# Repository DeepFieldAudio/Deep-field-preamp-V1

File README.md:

# Deep Field Preamp V1

A 4-way DIY dub preamp — open source, free, and built to be modified.

<!-- Render generated with:
     kicad-cli pcb render -o docs/images/board-top.png --quality high \
       --width 1800 --height 1080 --side top --background opaque --zoom 1.35 \
       hardware/deep-field-preamp.kicad_pcb
     Replace with a photo of a built unit when you have one. -->

## Features

- 4-way crossover with kill switches and level control per band
- 4-band parametric EQ
- 12-band graphic EQ
- Phono and line inputs for music sources
- 2 aux inputs
- 1 mic input
- 2 FX loops

## Project status

| Item | Version |
| --- | --- |
| Schematic / PCB source | V1 |
| Schematic PDF | V1 rev2 |
| Gerbers | V1.2 |

> **Note:** the source files, the PDF and the gerbers currently carry three
> different version labels. If you are ordering boards, treat
> `production/v1.2/` as the authoritative set and check it against the source
> before committing to a run.

## Repository layout

```
hardware/          KiCad 9 project — schematic, PCB and project file
docs/              Schematic PDF and build documentation
production/v1.2/   Gerbers and drill files, ready to send to a fab house
```

## Building one

1. **Order the boards.** Upload `production/v1.2/deep-field-preamp-v1.2-gerbers.zip`
   to your fab house of choice — it contains the gerbers, both drill files and
   the job file.
2. **Get the parts.** <!-- TODO: export a BOM from KiCad (File → Export → BOM)
   and commit it as docs/bom.csv, then link it here. -->
3. **Open the design.** `hardware/deep-field-preamp.kicad_pro` opens in
   KiCad 9.0 or newer. The schematic is also in `docs/` as a PDF if you just
   want to read it.

## Contributing

If you find a mistake I made, or a way to improve the design, please open an
issue or a pull request — I would rather have it fixed in the open than in
someone's private fork. And if you build your own Deep Field, share it! I would
love to see your builds.

## Licence

This work shall remain open source and free.

- **Hardware** (schematics, PCB layout, gerbers): [CERN Open Hardware Licence
  Version 2 — Strongly Reciprocal](LICENSE-hardware.txt) (CERN-OHL-S-2.0)
- **Documentation** (PDF, images, this README): [Creative Commons
  Attribution-ShareAlike 4.0 International](LICENSE-docs.txt) (CC BY-SA 4.0)

Both are share-alike: if you make your own version of this preamp, you are free
to build it, sell it and modify it, but you must publish your changes under the
same conditions I did.

## Contact

Deep Field Audio on Instagram and Facebook.

---

All you have here is work I spent countless hours on, and that I'm really happy
to share with you.

— Nélo Breuiller

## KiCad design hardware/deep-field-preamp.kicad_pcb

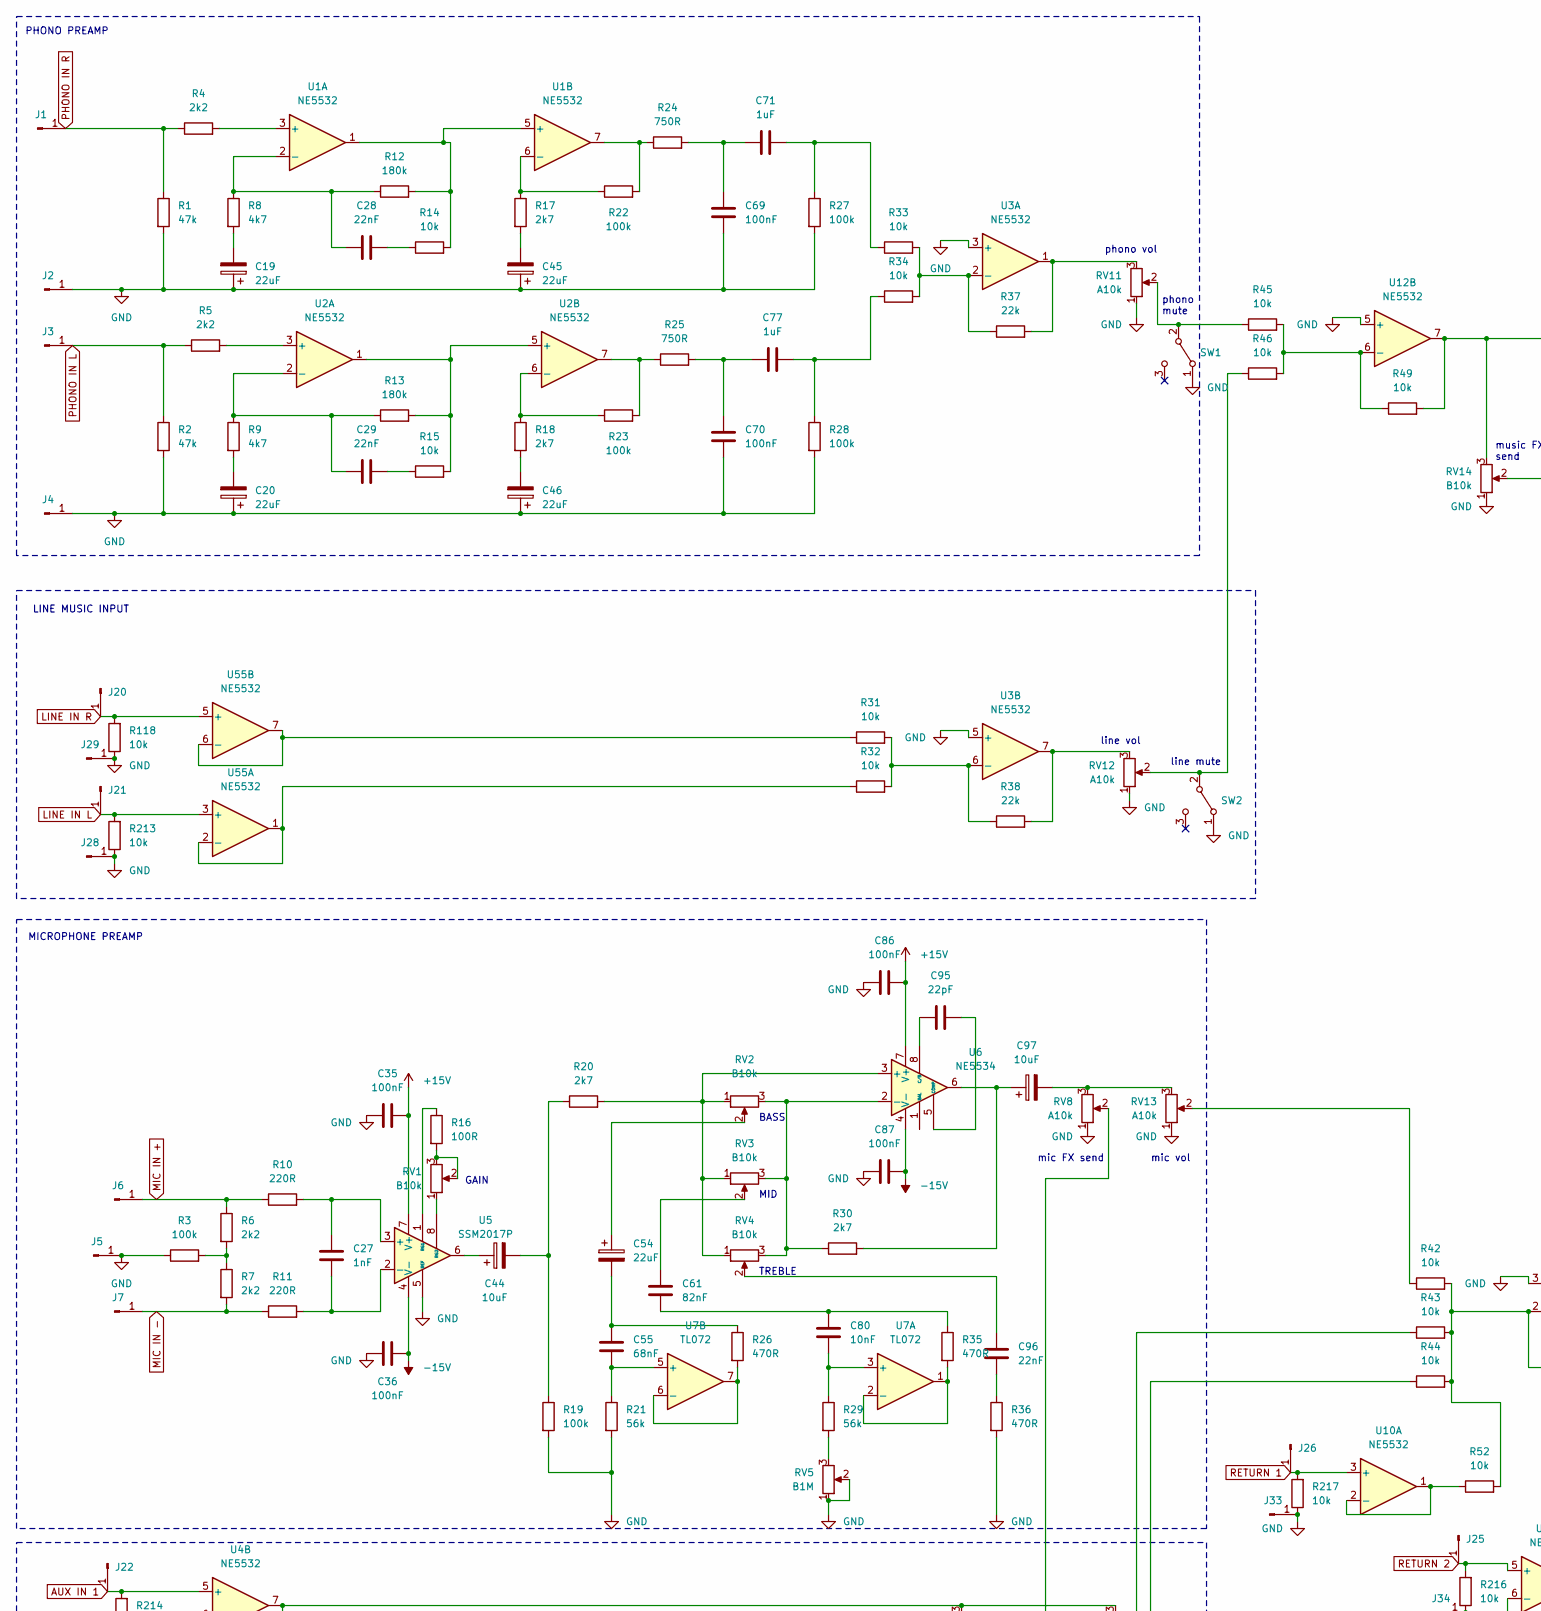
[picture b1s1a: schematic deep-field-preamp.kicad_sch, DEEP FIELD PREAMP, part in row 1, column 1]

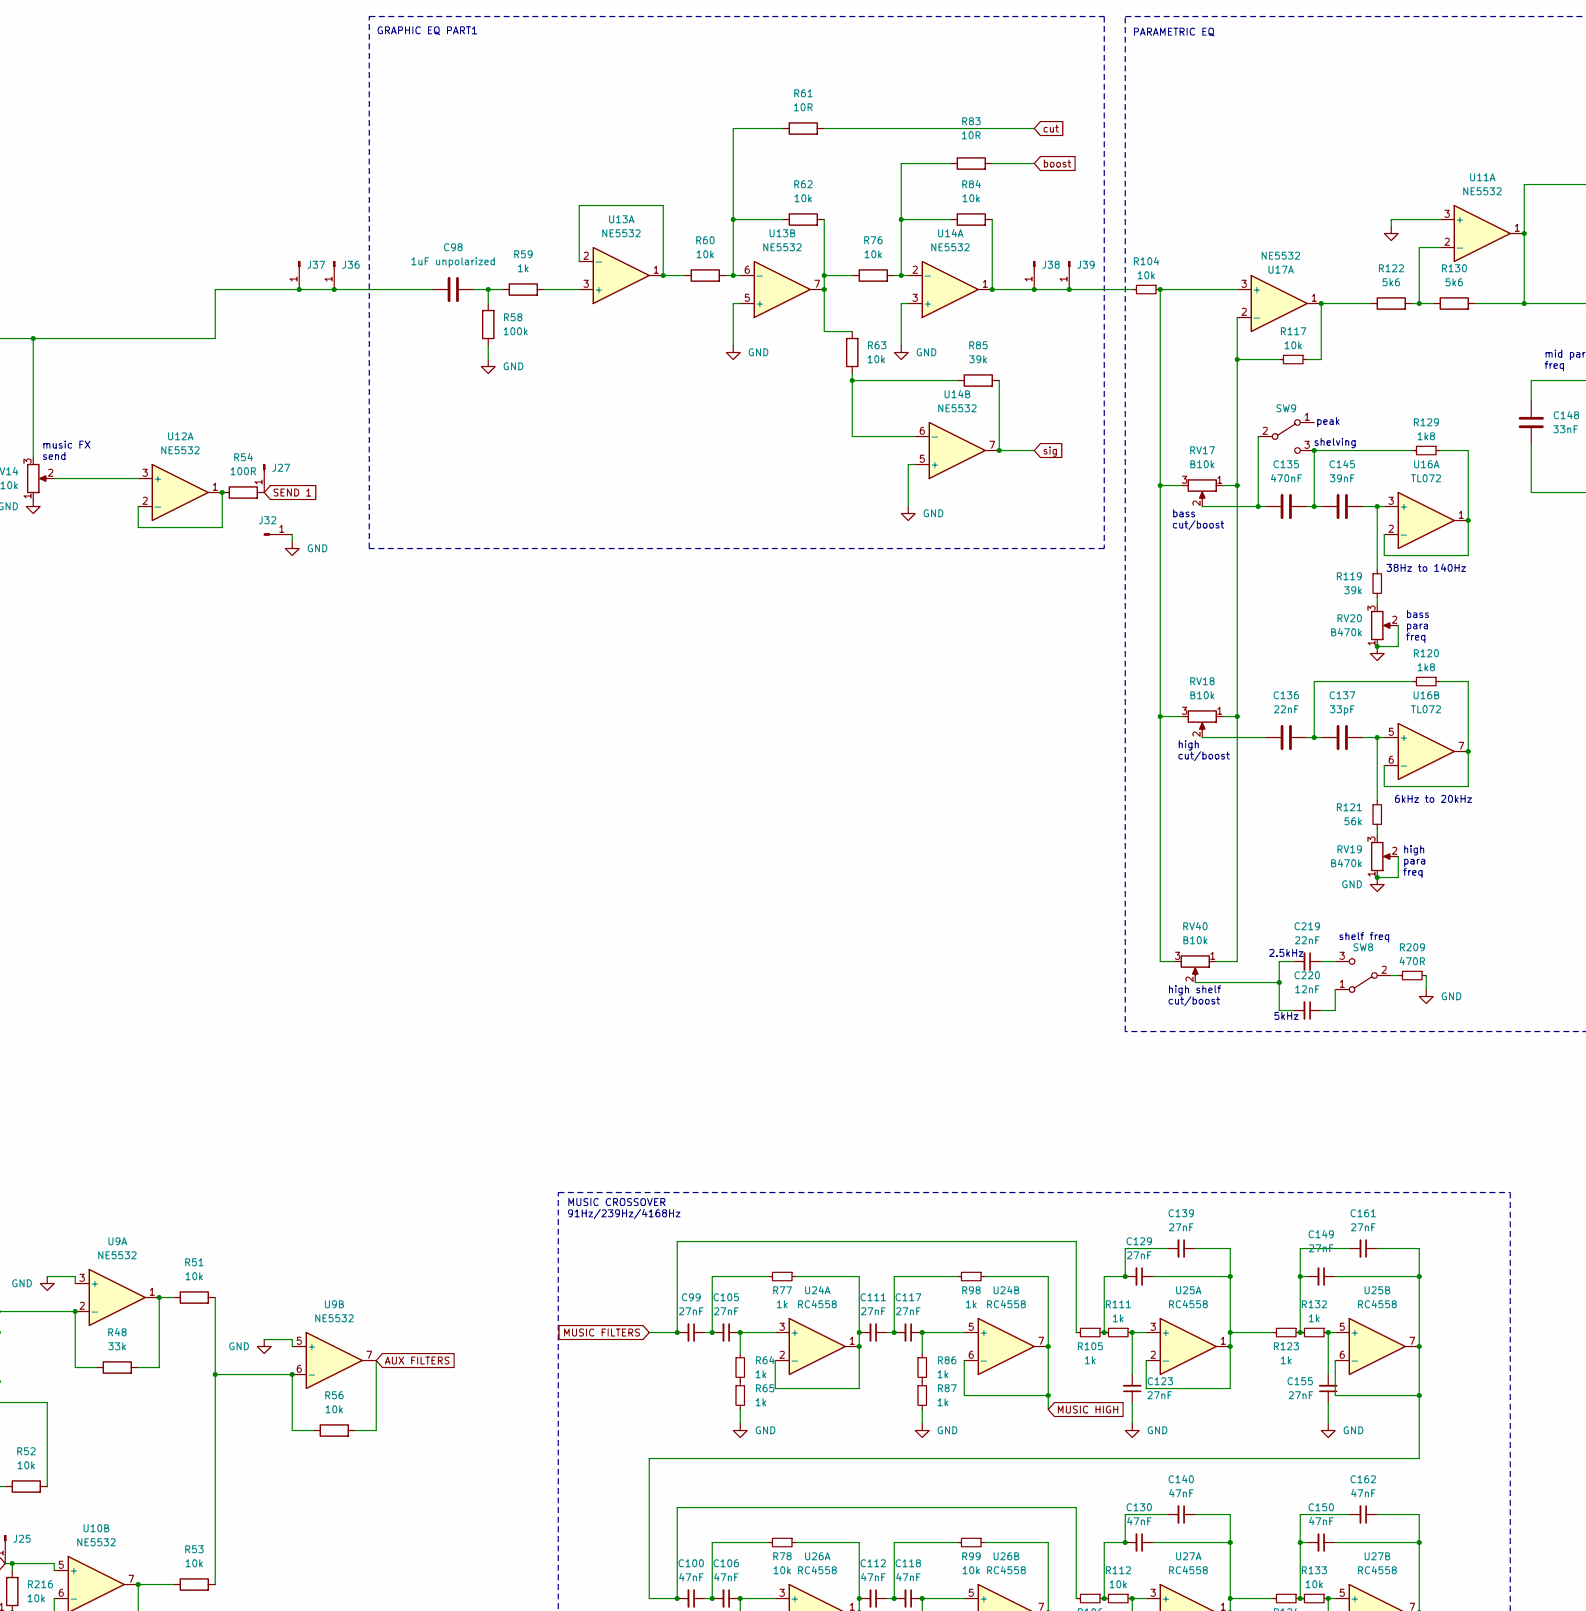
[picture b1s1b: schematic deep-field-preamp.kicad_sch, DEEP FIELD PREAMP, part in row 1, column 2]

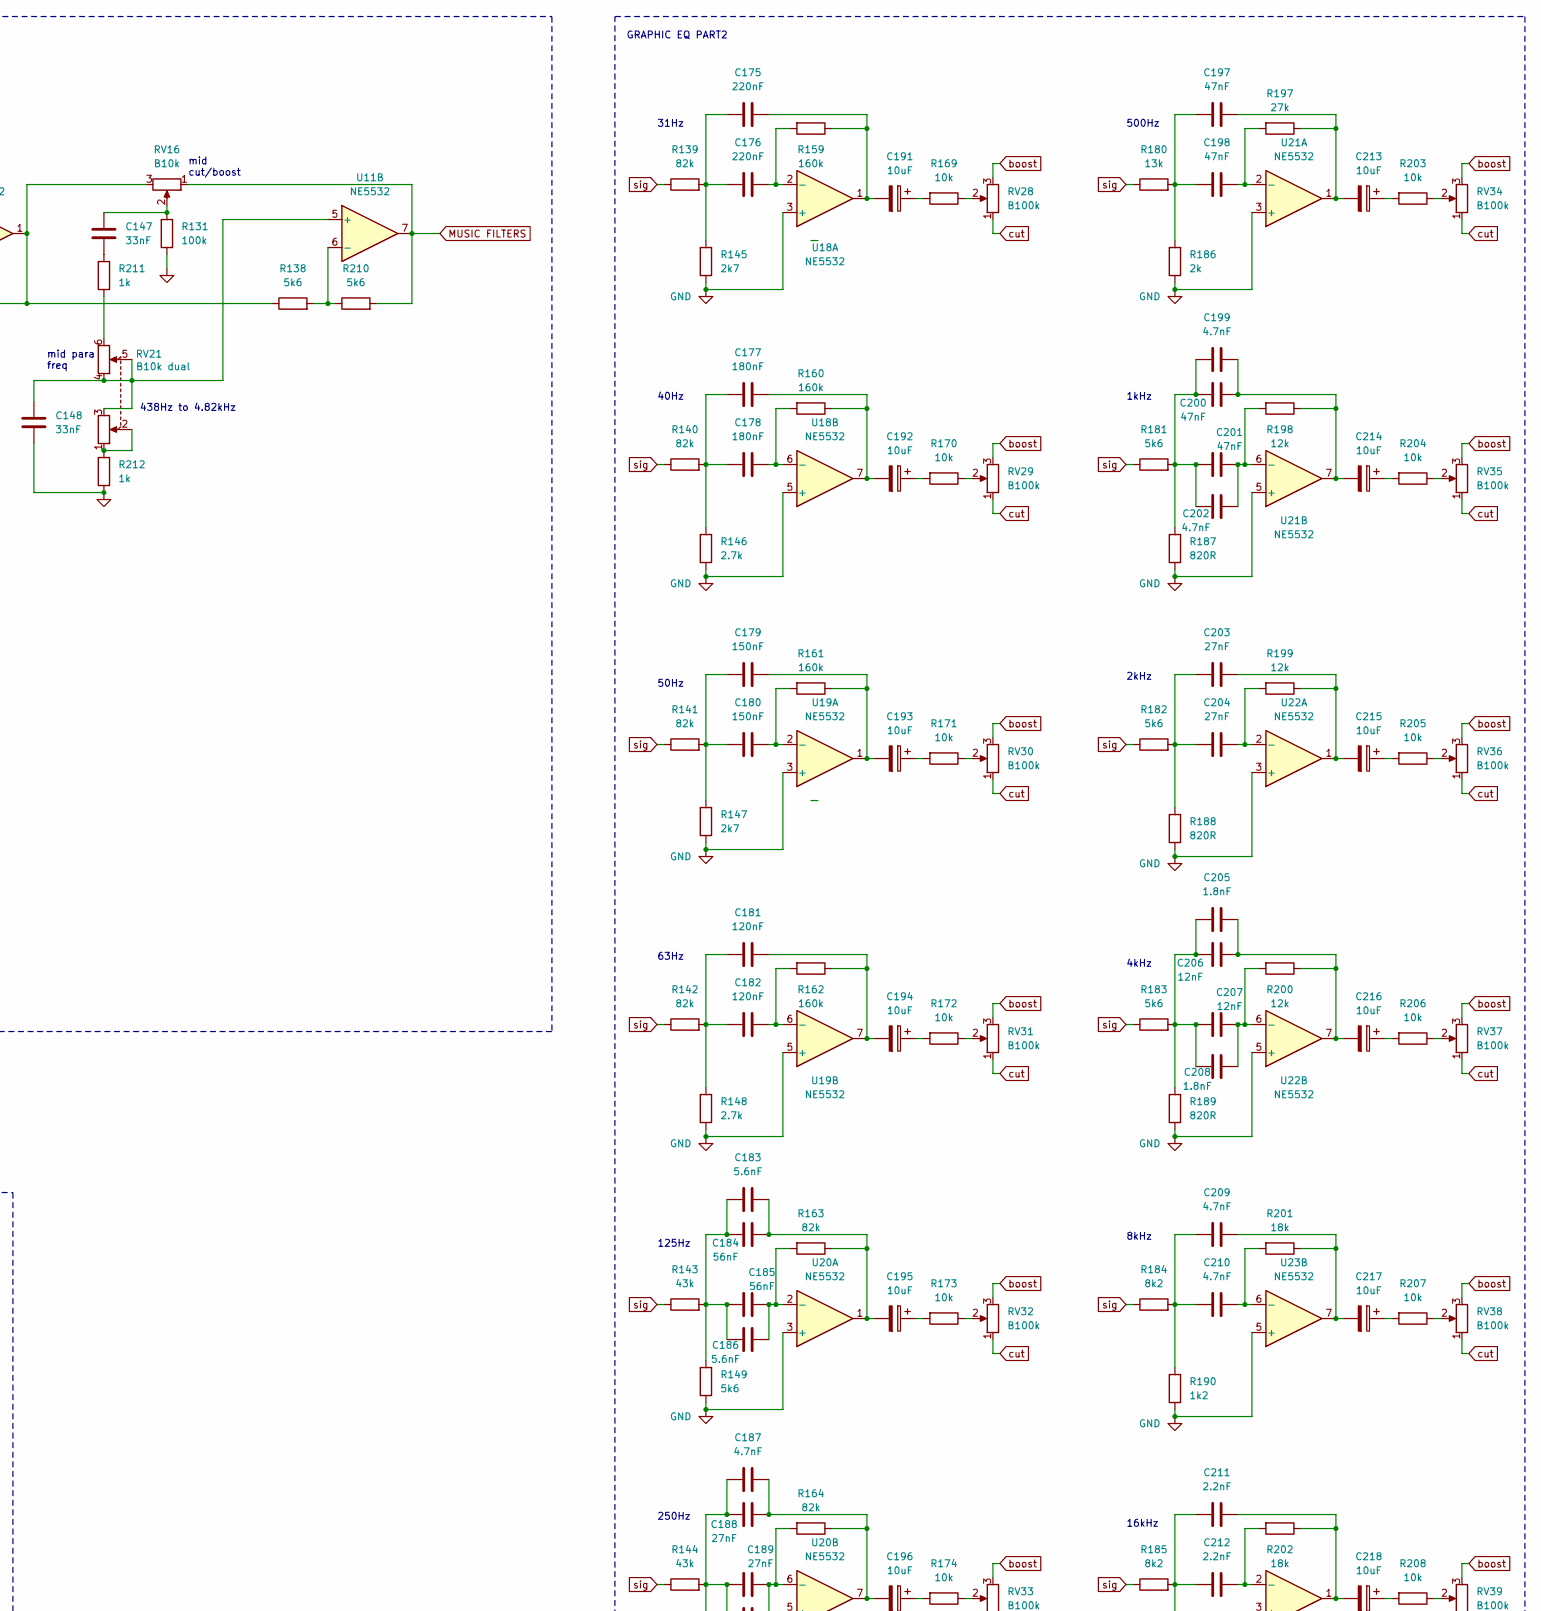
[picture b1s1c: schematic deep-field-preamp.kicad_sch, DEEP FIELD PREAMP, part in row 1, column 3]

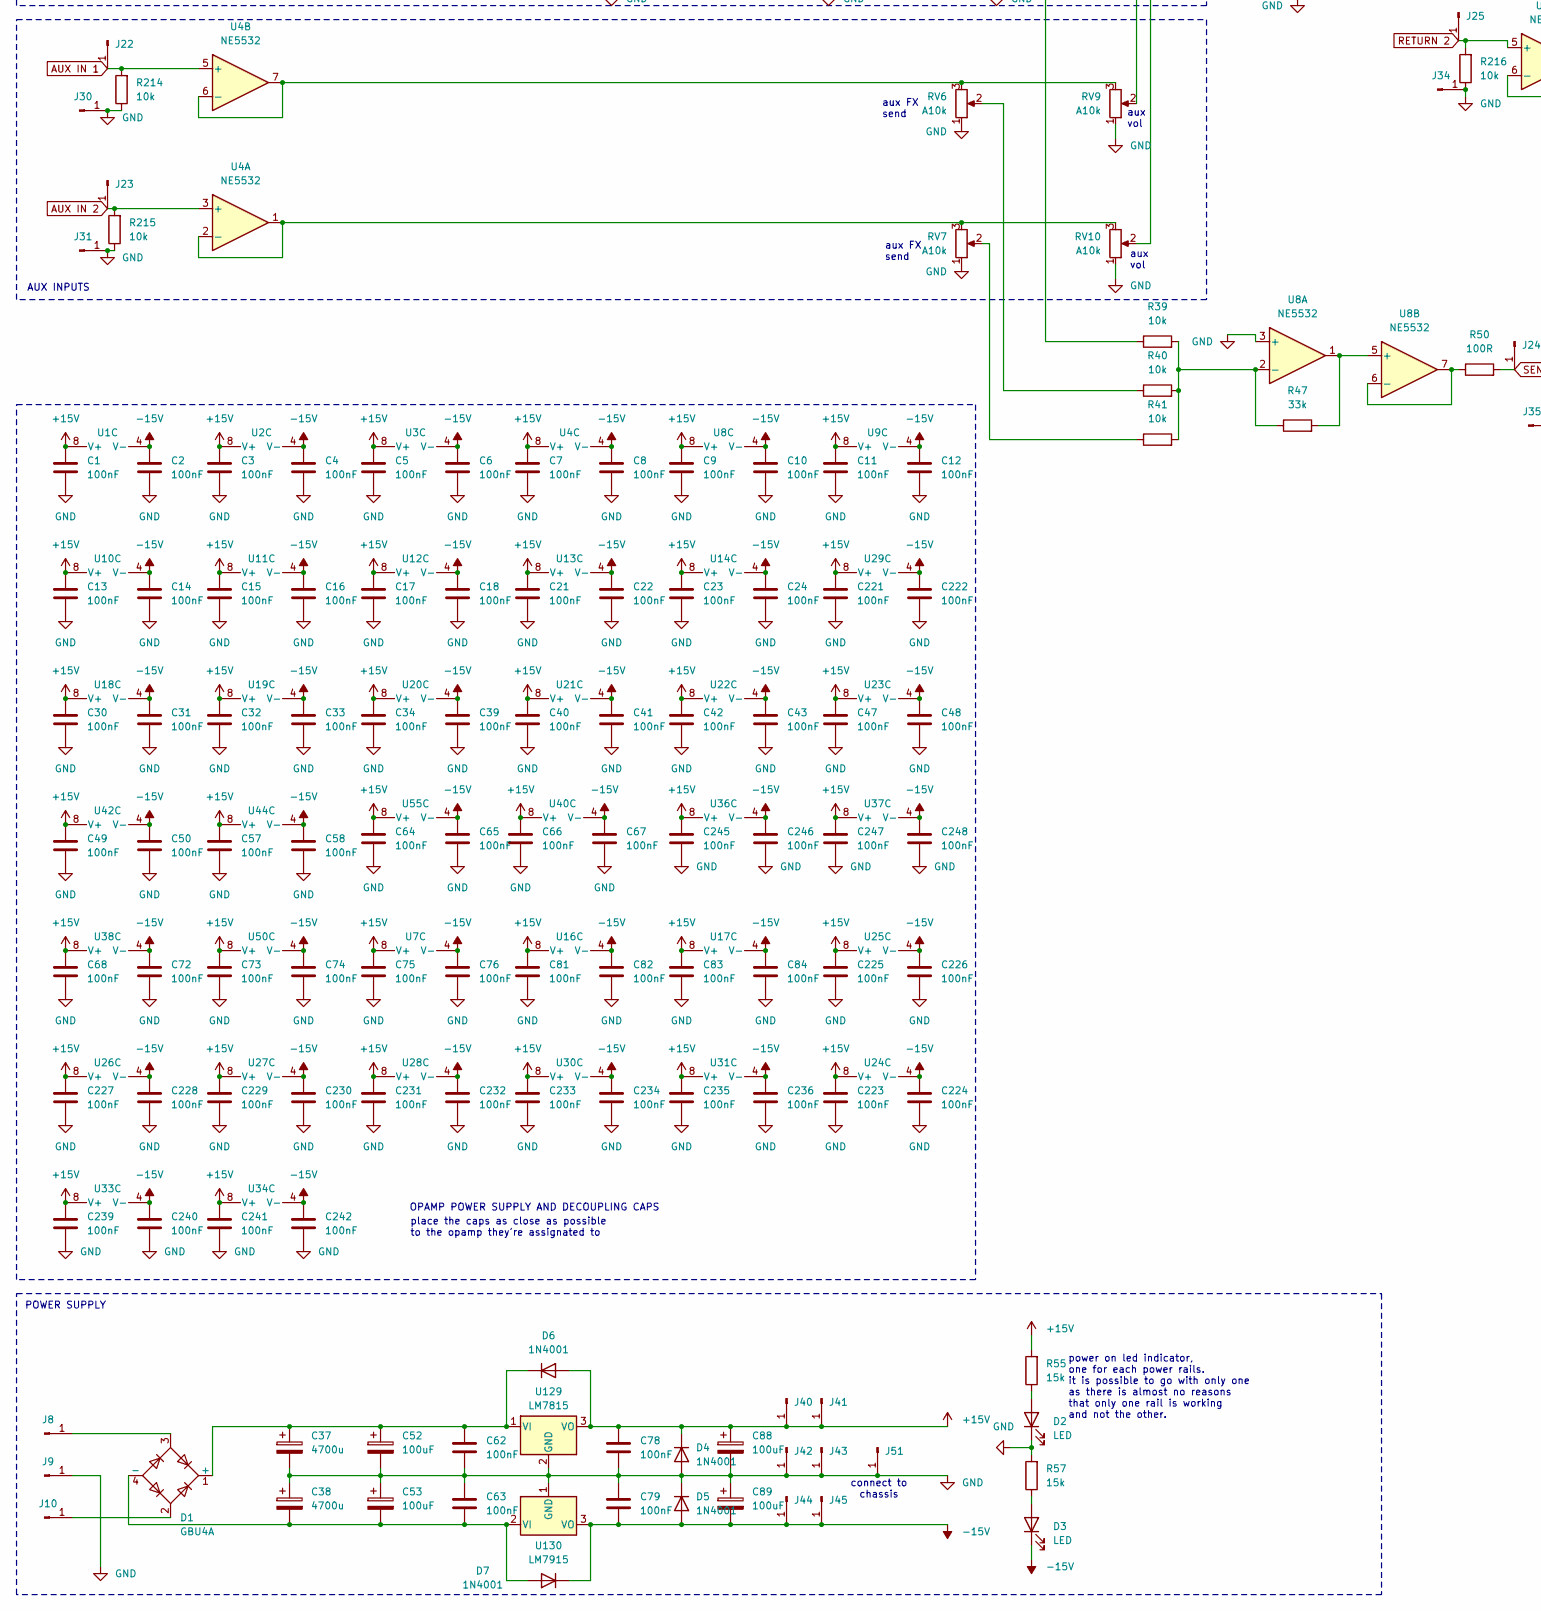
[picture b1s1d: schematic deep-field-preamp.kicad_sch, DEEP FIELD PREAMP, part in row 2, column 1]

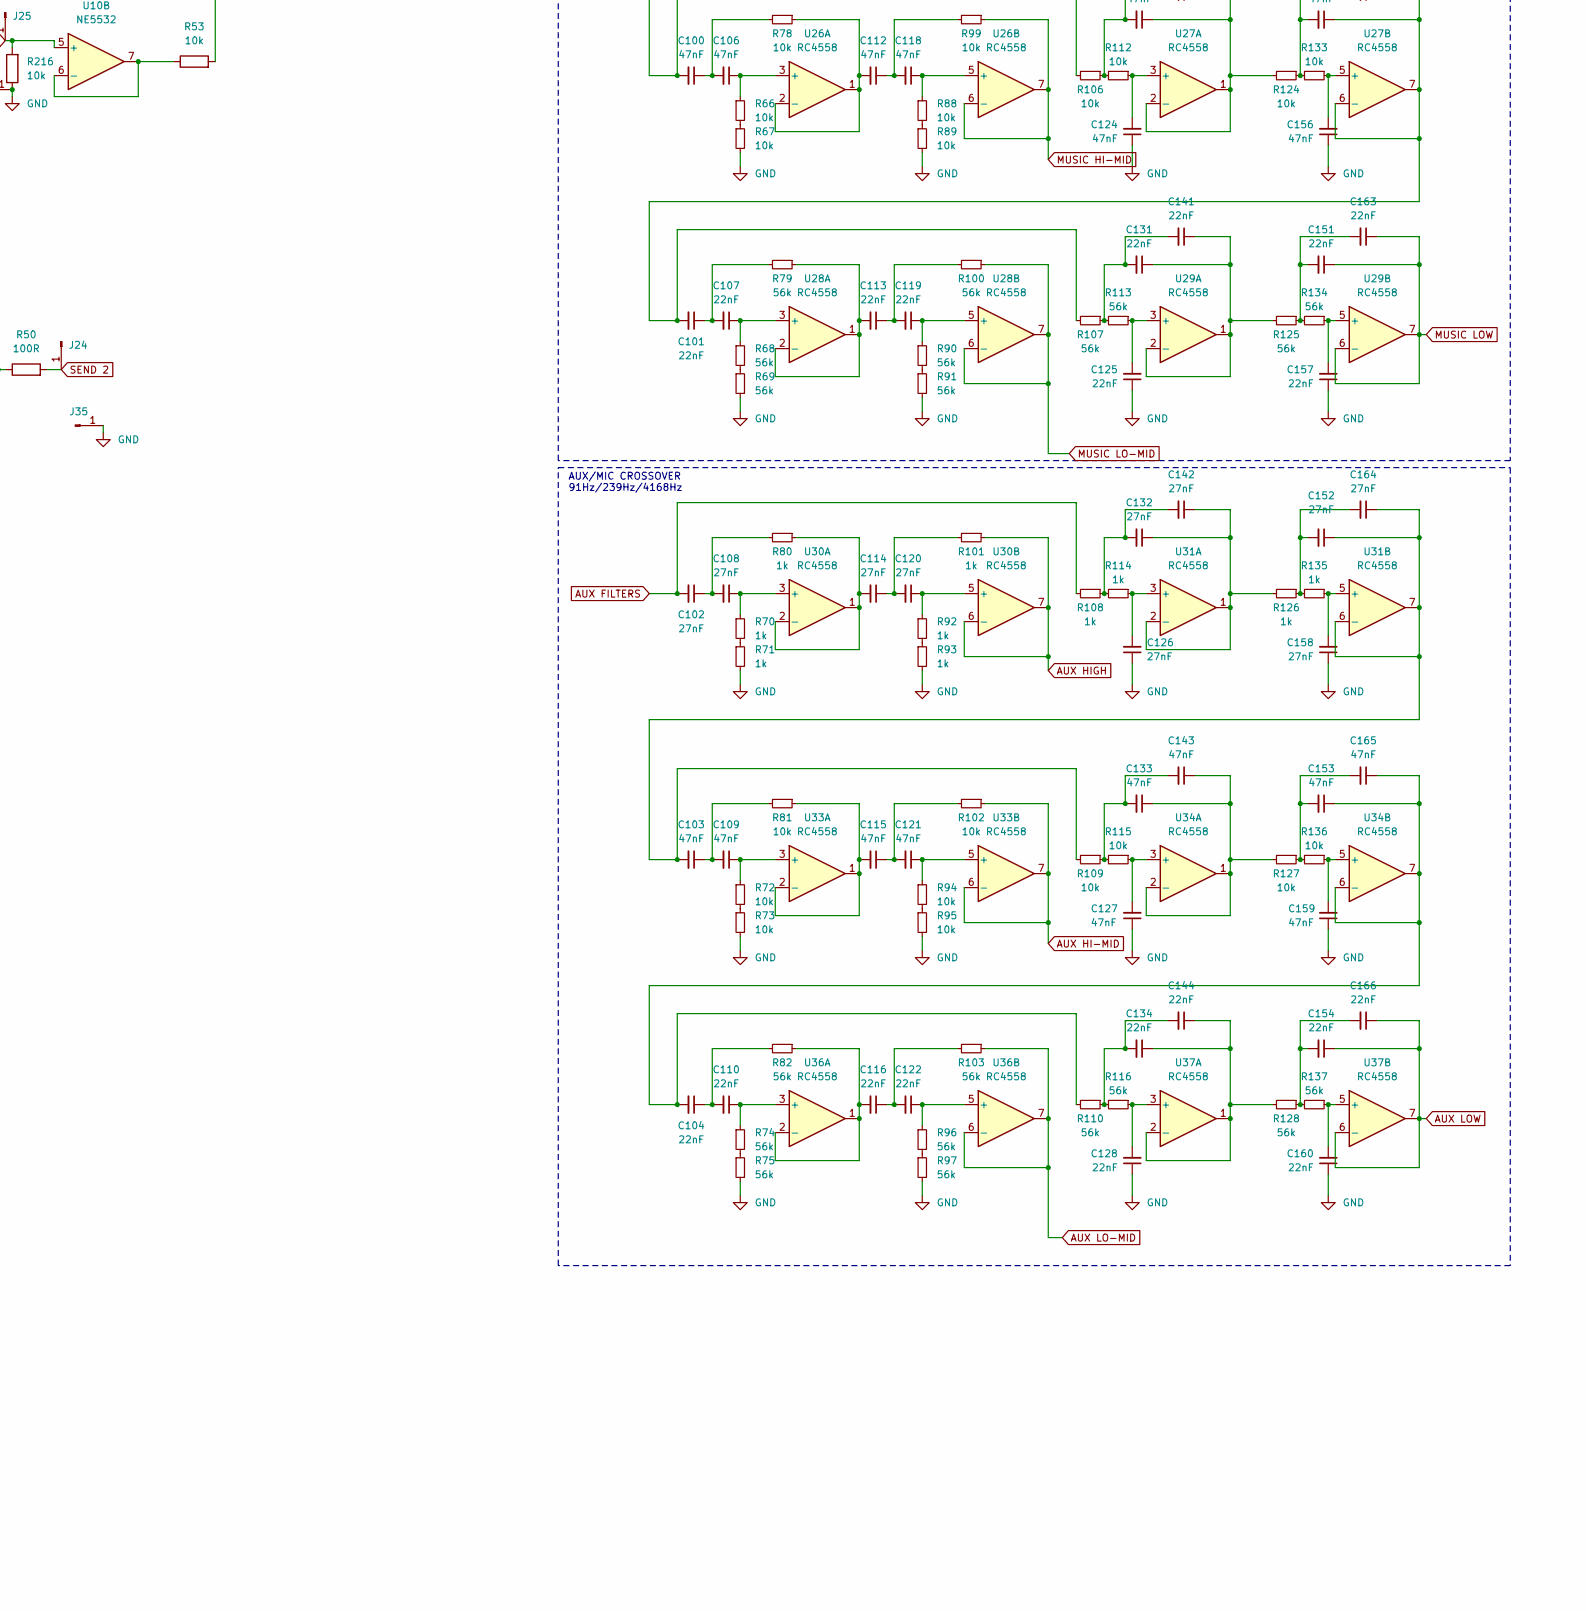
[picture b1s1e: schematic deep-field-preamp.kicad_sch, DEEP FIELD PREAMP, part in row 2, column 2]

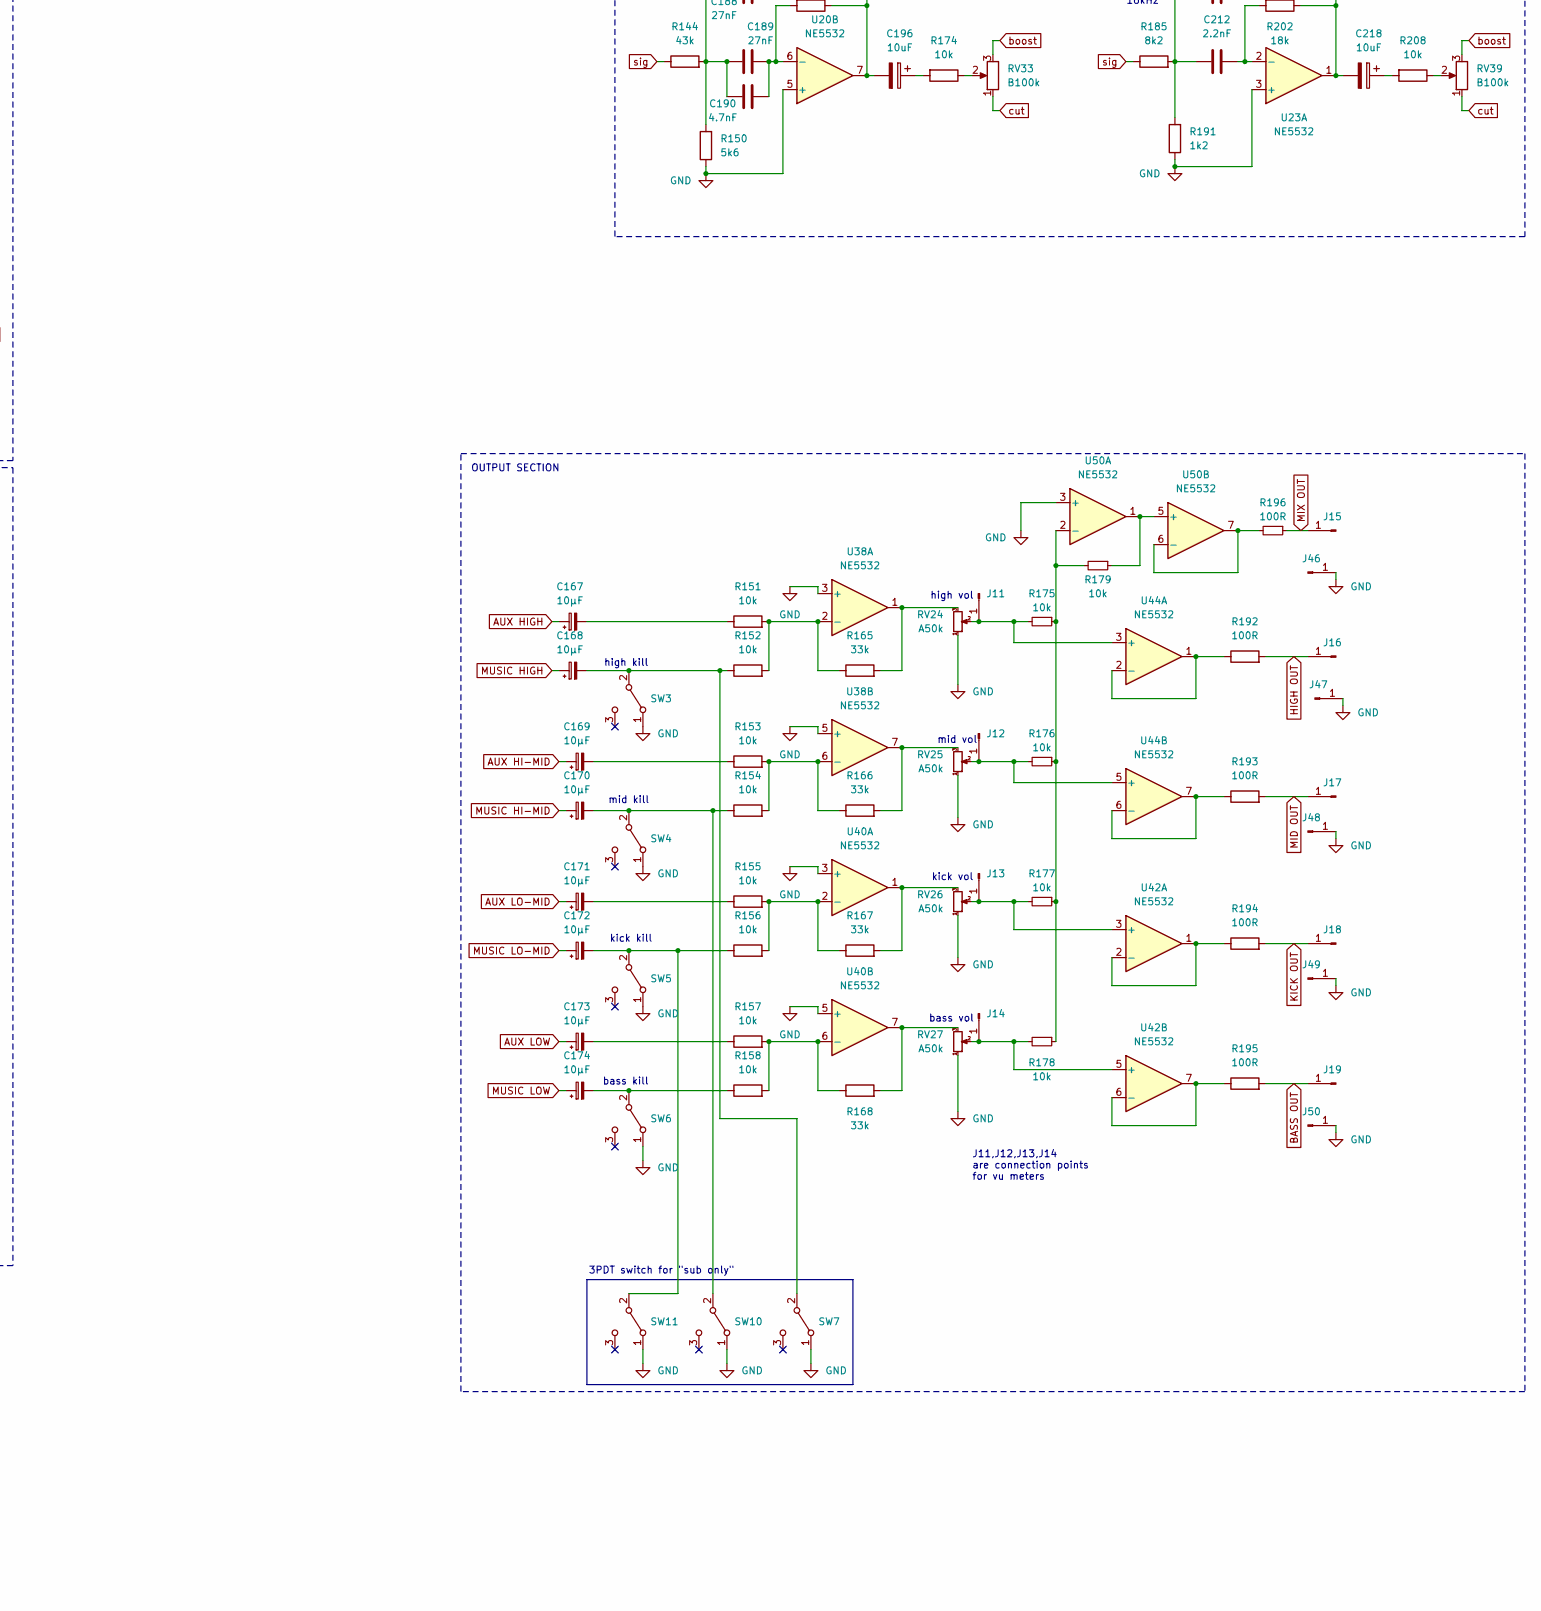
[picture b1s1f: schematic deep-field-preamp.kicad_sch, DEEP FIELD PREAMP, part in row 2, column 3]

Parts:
C1, C2, C3, C4, C5, C6, C7, C8, C9, C10, C11, C12, C13, C14, C15, C16, C17, C18, C21, C22, C23, C24, C30, C31, C32, C33, C34, C39, C40, C41, C42, C43, C47, C48, C49, C50, C57, C58, C62, C63, C64, C65, C66, C67, C68, C72, C73, C74, C75, C76, C78, C79, C81, C82, C83, C84, C221, C222, C223, C224, C225, C226, C227, C228, C229, C230, C231, C232, C233, C234, C235, C236, C239, C240, C241, C242, C245, C246, C247, C248: 100nF; C_Rect_L11.5mm_W4.3mm_P10.00mm_MKT
C19, C20, C45, C46, C54: 22uF; CP_Radial_D5.0mm_P2.50mm
C27: 1nF; C_Rect_L11.5mm_W6.9mm_P10.00mm_MKT
C28, C29: 22nF; C_Rect_L7.2mm_W3.5mm_P5.00mm_FKS2_FKP2_MKS2_MKP2
C35, C36, C69, C70, C86, C87: 100nF; C_Rect_L7.2mm_W3.5mm_P5.00mm_FKS2_FKP2_MKS2_MKP2
C37, C38: 4700u; CP_Radial_D18.0mm_P7.50mm
C44, C97, C191, C192, C193, C194, C195, C196, C213, C214, C215, C216, C217, C218: 10uF; CP_Radial_D5.0mm_P2.50mm
C52, C53, C88, C89: 100uF; CP_Radial_D6.3mm_P2.50mm
C55: 68nF; C_Rect_L10.3mm_W7.2mm_P7.50mm_MKS4
C61: 82nF; C_Rect_L10.3mm_W7.2mm_P7.50mm_MKS4
C71, C77: 1uF; C_Rect_L10.3mm_W7.2mm_P7.50mm_MKS4
C80: 10nF; C_Rect_L10.3mm_W7.2mm_P7.50mm_MKS4
C95: 22pF; C_Disc_D7.5mm_W5.0mm_P5.00mm
C96: 22nF; C_Rect_L9.0mm_W8.5mm_P7.50mm_MKT
C98: 1uF unpolarized; C_Rect_L11.5mm_W4.3mm_P10.00mm_MKT
C99, C102, C105, C108, C111, C114, C117, C120, C123, C126, C129, C132, C139, C142, C149, C152, C155, C158, C161, C164, C188, C189, C203, C204: 27nF; C_Rect_L11.5mm_W4.3mm_P10.00mm_MKT
C100, C103, C106, C109, C112, C115, C118, C121, C124, C127, C130, C133, C140, C143, C150, C153, C156, C159, C162, C165, C197, C198, C200, C201: 47nF; C_Rect_L11.5mm_W4.3mm_P10.00mm_MKT
C101, C104, C107, C110, C113, C116, C119, C122, C125, C128, C131, C134, C136, C141, C144, C151, C154, C157, C160, C163, C166, C219: 22nF; C_Rect_L11.5mm_W4.3mm_P10.00mm_MKT
C135: 470nF; C_Rect_L11.5mm_W4.3mm_P10.00mm_MKT
C137: 33pF; C_Rect_L11.5mm_W4.3mm_P10.00mm_MKT
C145: 39nF; C_Rect_L11.5mm_W4.3mm_P10.00mm_MKT
C147, C148: 33nF; C_Rect_L11.5mm_W4.3mm_P10.00mm_MKT
C167, C168, C169, C170, C171, C172, C173, C174: 10µF; CP_Radial_D5.0mm_P2.50mm
C175, C176: 220nF; C_Rect_L11.5mm_W4.3mm_P10.00mm_MKT
C177, C178: 180nF; C_Rect_L11.5mm_W4.3mm_P10.00mm_MKT
C179, C180: 150nF; C_Rect_L11.5mm_W4.3mm_P10.00mm_MKT
C181, C182: 120nF; C_Rect_L11.5mm_W4.3mm_P10.00mm_MKT
C183, C186: 5.6nF; C_Rect_L11.5mm_W4.3mm_P10.00mm_MKT
C184, C185: 56nF; C_Rect_L11.5mm_W4.3mm_P10.00mm_MKT
C187, C190, C199, C202, C209, C210: 4.7nF; C_Rect_L11.5mm_W4.3mm_P10.00mm_MKT
C205, C208: 1.8nF; C_Rect_L11.5mm_W4.3mm_P10.00mm_MKT
C206, C207, C220: 12nF; C_Rect_L11.5mm_W4.3mm_P10.00mm_MKT
C211, C212: 2.2nF; C_Rect_L11.5mm_W4.3mm_P10.00mm_MKT
D1: GBU4A; Diode_Bridge_Vishay_GBU
D2, D3: LED; LED_D5.0mm
D4, D5, D6, D7: 1N4001; D_DO-41_SOD81_P10.16mm_Horizontal
J1, J2, J3, J4, J5, J6, J7, J15, J16, J17, J18, J19, J20, J21, J22, J23, J24, J25, J26, J27, J28, J29, J30, J31, J32, J33, J34, J35, J36, J37, J38, J39, J40, J41, J42, J43, J44, J45, J46, J47, J48, J49, J50: Conn_01x01_Pin; SolderWire-0.75sqmm_1x01_D1.25mm_OD2.3mm
J8, J9, J10, J51: Conn_01x01_Pin; SolderWire-2.5sqmm_1x01_D2.4mm_OD4.4mm
J11, J12, J13, J14: SolderWire-0.75sqmm_1x01_D1.25mm_OD2.3mm
R1, R2: 47k; R_Axial_DIN0207_L6.3mm_D2.5mm_P10.16mm_Horizontal
R3, R19, R22, R23, R27, R28, R58, R131: 100k; R_Axial_DIN0207_L6.3mm_D2.5mm_P10.16mm_Horizontal
R4, R5, R6, R7: 2k2; R_Axial_DIN0207_L6.3mm_D2.5mm_P10.16mm_Horizontal
R8, R9: 4k7; R_Axial_DIN0207_L6.3mm_D2.5mm_P10.16mm_Horizontal
R10, R11: 220R; R_Axial_DIN0207_L6.3mm_D2.5mm_P10.16mm_Horizontal
R12, R13: 180k; R_Axial_DIN0207_L6.3mm_D2.5mm_P10.16mm_Horizontal
R14, R15, R31, R32, R33, R34, R39, R40, R41, R42, R43, R44, R45, R46, R49, R51, R52, R53, R56, R60, R62, R63, R66, R67, R72, R73, R76, R78, R81, R84, R88, R89, R94, R95, R99, R102, R104, R106, R109, R112, R115, R117, R118, R124, R127, R133, R136, R151, R152, R153, R154, R155, R156, R157, R158, R169, R170, R171, R172, R173, R174, R175, R176, R177, R178, R179, R203, R204, R205, R206, R207, R208, R213, R214, R215, R216, R217: 10k; R_Axial_DIN0207_L6.3mm_D2.5mm_P10.16mm_Horizontal
R16, R50, R54, R192, R193, R194, R195, R196: 100R; R_Axial_DIN0207_L6.3mm_D2.5mm_P10.16mm_Horizontal
R17, R18, R20, R30, R145, R147: 2k7; R_Axial_DIN0207_L6.3mm_D2.5mm_P10.16mm_Horizontal
R21, R29, R68, R69, R74, R75, R79, R82, R90, R91, R96, R97, R100, R103, R107, R110, R113, R116, R121, R125, R128, R134, R137: 56k; R_Axial_DIN0207_L6.3mm_D2.5mm_P10.16mm_Horizontal
R24, R25: 750R; R_Axial_DIN0207_L6.3mm_D2.5mm_P10.16mm_Horizontal
R26, R35, R36, R209: 470R; R_Axial_DIN0207_L6.3mm_D2.5mm_P10.16mm_Horizontal
R37, R38: 22k; R_Axial_DIN0207_L6.3mm_D2.5mm_P10.16mm_Horizontal
R47, R48, R165, R166, R167, R168: 33k; R_Axial_DIN0207_L6.3mm_D2.5mm_P10.16mm_Horizontal
R55, R57: 15k; R_Axial_DIN0309_L9.0mm_D3.2mm_P12.70mm_Horizontal
R59, R64, R65, R70, R71, R77, R80, R86, R87, R92, R93, R98, R101, R105, R108, R111, R114, R123, R126, R132, R135, R211, R212: 1k; R_Axial_DIN0207_L6.3mm_D2.5mm_P10.16mm_Horizontal
R61, R83: 10R; R_Axial_DIN0207_L6.3mm_D2.5mm_P10.16mm_Horizontal
R85, R119: 39k; R_Axial_DIN0207_L6.3mm_D2.5mm_P10.16mm_Horizontal
R120, R129: 1k8; R_Axial_DIN0207_L6.3mm_D2.5mm_P10.16mm_Horizontal
R122, R130, R138, R149, R150, R181, R182, R183, R210: 5k6; R_Axial_DIN0207_L6.3mm_D2.5mm_P10.16mm_Horizontal
R139, R140, R141, R142, R163, R164: 82k; R_Axial_DIN0207_L6.3mm_D2.5mm_P10.16mm_Horizontal
R143, R144: 43k; R_Axial_DIN0207_L6.3mm_D2.5mm_P10.16mm_Horizontal
R146, R148: 2.7k; R_Axial_DIN0207_L6.3mm_D2.5mm_P10.16mm_Horizontal
R159, R160, R161, R162: 160k; R_Axial_DIN0207_L6.3mm_D2.5mm_P10.16mm_Horizontal
R180: 13k; R_Axial_DIN0207_L6.3mm_D2.5mm_P10.16mm_Horizontal
R184, R185: 8k2; R_Axial_DIN0207_L6.3mm_D2.5mm_P10.16mm_Horizontal
R186: 2k; R_Axial_DIN0207_L6.3mm_D2.5mm_P10.16mm_Horizontal
R187, R188, R189: 820R; R_Axial_DIN0207_L6.3mm_D2.5mm_P10.16mm_Horizontal
R190, R191: 1k2; R_Axial_DIN0207_L6.3mm_D2.5mm_P10.16mm_Horizontal
R197: 27k; R_Axial_DIN0207_L6.3mm_D2.5mm_P10.16mm_Horizontal
R198, R199, R200: 12k; R_Axial_DIN0207_L6.3mm_D2.5mm_P10.16mm_Horizontal
R201, R202: 18k; R_Axial_DIN0207_L6.3mm_D2.5mm_P10.16mm_Horizontal
RV1, RV2, RV3, RV4, RV14, RV16, RV17, RV18, RV40: B10k; Molex_KK-254_AE-6410-03A_1x03_P2.54mm_Vertical
RV5: B1M; Molex_KK-254_AE-6410-03A_1x03_P2.54mm_Vertical
RV6, RV7, RV8, RV9, RV10, RV11, RV12, RV13: A10k; Molex_KK-254_AE-6410-03A_1x03_P2.54mm_Vertical
RV19, RV20: B470k; Molex_KK-254_AE-6410-03A_1x03_P2.54mm_Vertical
RV21: B10k dual; Molex_KK-254_AE-6410-06A_1x06_P2.54mm_Vertical
RV24, RV25, RV26, RV27: A50k; Molex_KK-254_AE-6410-03A_1x03_P2.54mm_Vertical
RV28, RV29, RV30, RV31, RV32, RV33, RV34, RV35, RV36, RV37, RV38, RV39: B100k; potentiometer_Alpha_RV16AF41_Single_Horizontal
SW1, SW2, SW3, SW4, SW5, SW6, SW7, SW8, SW9, SW10, SW11: SW_SPDT; Molex_KK-254_AE-6410-03A_1x03_P2.54mm_Vertical
U1, U2, U8, U10, U12, U55: NE5532; DIP-8_W7.62mm_LongPads
U3, U4, U9, U11, U13, U14, U17, U18, U19, U20, U21, U22, U23, U38, U40, U42, U44, U50: NE5532; DIP-8_W7.62mm_Socket_LongPads
U5: SSM2017P; DIP-8_W7.62mm
U6: NE5534; DIP-8_W7.62mm
U7: TL072; DIP-8_W7.62mm
U16: TL072; DIP-8_W7.62mm_Socket_LongPads
U24, U25, U26, U27, U28, U29, U30, U31, U33, U34, U36, U37: RC4558; DIP-8_W7.62mm_Socket_LongPads
U129: LM7815; TO-220-3_Vertical
U130: LM7915; TO-220-3_Vertical

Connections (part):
+15V: C1.1, C3.1, C5.1, C7.1, C9.1, C11.1, C13.1, C15.1, C17.1, C21.1, C23.1, C30.1, C32.1, C34.1, C35.2, C40.1, C42.1, C47.1, C49.1, C57.1, C64.1, C66.1, C68.1, C73.1, C75.1, C78.1, C81.1, C83.1, C86.2, C88.1, C221.1, C223.1, C225.1, C227.1, C229.1, C231.1, C233.1, C235.1, C239.1, C241.1, C245.1, C247.1, D4.1 (K), D6.2 (A), J40.1, J41.1, R55.2, U1.8 (V+), U2.8 (V+), U3.8 (V+), U4.8 (V+), U5.7 (V+), U6.7 (V+), U7.8 (V+), U8.8 (V+), U9.8 (V+), U10.8 (V+), U11.8 (V+), U12.8 (V+), U13.8 (V+), U14.8 (V+), U16.8 (V+), U17.8 (V+), U18.8 (V+), U19.8 (V+), U20.8 (V+), U21.8 (V+), U22.8 (V+), U23.8 (V+), U24.8 (V+), U25.8 (V+), U26.8 (V+), U27.8 (V+), U28.8 (V+), U29.8 (V+), U30.8 (V+), U31.8 (V+), U33.8 (V+), U34.8 (V+), U36.8 (V+)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
-15V: C2.1, C4.1, C6.1, C8.1, C10.1, C12.1, C14.1, C16.1, C18.1, C22.1, C24.1, C31.1, C33.1, C36.2, C39.1, C41.1, C43.1, C48.1, C50.1, C58.1, C65.1, C67.1, C72.1, C74.1, C76.1, C79.2, C82.1, C84.1, C87.2, C89.2, C222.1, C224.1, C226.1, C228.1, C230.1, C232.1, C234.1, C236.1, C240.1, C242.1, C246.1, C248.1, D3.1 (K), D5.2 (A), D7.1 (K), J44.1, J45.1, U1.4 (V-), U2.4 (V-), U3.4 (V-), U4.4 (V-), U5.4 (V-), U6.4 (V-), U7.4 (V-), U8.4 (V-), U9.4 (V-), U10.4 (V-), U11.4 (V-), U12.4 (V-), U13.4 (V-), U14.4 (V-), U16.4 (V-), U17.4 (V-), U18.4 (V-), U19.4 (V-), U20.4 (V-), U21.4 (V-), U22.4 (V-), U23.4 (V-), U24.4 (V-), U25.4 (V-), U26.4 (V-), U27.4 (V-), U28.4 (V-), U29.4 (V-), U30.4 (V-), U31.4 (V-), U33.4 (V-), U34.4 (V-), U36.4 (V-)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
AUX FILTERS: C102.2, R56.2, R108.2, U9.7
AUX HI-MID: C169.1, R102.1, U33.6 (-), U33.7
AUX HIGH: C167.1, R101.1, U30.6 (-), U30.7
AUX IN 1: J22.1, R214.2, U4.5 (+)
AUX IN 2: J23.1, R215.2, U4.3 (+)
AUX LO-MID: C171.1, R103.1, U36.6 (-), U36.7
AUX LOW: C154.1, C166.1, C173.1, U37.6 (-), U37.7
BASS OUT: J19.1, R195.2
GND: C1.2, C2.2, C3.2, C4.2, C5.2, C6.2, C7.2, C8.2, C9.2, C10.2, C11.2, C12.2, C13.2, C14.2, C15.2, C16.2, C17.2, C18.2, C19.1, C20.1, C21.2, C22.2, C23.2, C24.2, C30.2, C31.2, C32.2, C33.2, C34.2, C35.1, C36.1, C37.2, C38.1, C39.2, C40.2, C41.2, C42.2, C43.2, C45.1, C46.1, C47.2, C48.2, C49.2, C50.2, C52.2, C53.1, C57.2, C58.2, C62.2, C63.1, C64.2, C65.2, C66.2, C67.2, C68.2, C69.2, C70.2, C72.2, C73.2, C74.2, C75.2, C76.2, C78.2, C79.1, C81.2, C82.2, C83.2, C84.2, C86.1, C87.1, C88.2, C89.1, C123.1, C124.1, C125.1, C126.1, C127.1, C128.1, C148.2, C155.1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
HIGH OUT: J16.1, R192.2
KICK OUT: J18.1, R194.2
LINE IN L: J21.1, R213.2, U55.3 (+)
LINE IN R: J20.1, R118.2, U55.5 (+)
MIC IN +: J6.1, R6.1, R10.1
MIC IN -: J7.1, R7.2, R11.1
MID OUT: J17.1, R193.2
MIX OUT: J15.1, R196.1
MUSIC FILTERS: C99.2, R105.2, R210.2, RV16.1, U11.7
MUSIC HI-MID: C170.1, R99.1, U26.6 (-), U26.7
MUSIC HIGH: C168.1, R98.1, U24.6 (-), U24.7
MUSIC LO-MID: C172.1, R100.1, U28.6 (-), U28.7
MUSIC LOW: C151.1, C163.1, C174.1, U29.6 (-), U29.7
unnamed: C19.2, R8.2
unnamed: C20.2, R9.2
unnamed: C28.2, R14.1
unnamed: C29.2, R15.1
unnamed: C44.1, U5.6
unnamed: C44.2, R19.1, R20.1
unnamed: C45.2, R17.2
unnamed: C46.2, R18.2
unnamed: C54.1, RV2.2
unnamed: C54.2, C55.1, R26.1
unnamed: C61.1, RV3.2
unnamed: C61.2, C80.2, R35.1
unnamed: C69.1, C71.1, R24.2
unnamed: C70.1, C77.1, R25.2
unnamed: C71.2, R27.1, R33.1
unnamed: C77.2, R28.1, R34.1
unnamed: C96.1, RV4.2
unnamed: C96.2, R36.1
unnamed: C97.1, R30.2, U6.6
unnamed: C97.2, RV8.3, RV13.3
unnamed: C98.2, R58.2, R59.1
unnamed: C100.1, C106.2, R78.2
unnamed: C101.1, C107.2, R79.2
unnamed: C102.1, C108.2, R80.2
unnamed: C103.1, C109.2, R81.2
unnamed: C104.1, C110.2, R82.2
unnamed: C99.1, C105.2, R77.2
unnamed: C111.1, C117.2, R98.2
unnamed: C112.1, C118.2, R99.2
unnamed: C113.1, C119.2, R100.2
unnamed: C114.1, C120.2, R101.2
unnamed: C115.1, C121.2, R102.2
unnamed: C116.1, C122.2, R103.2
unnamed: C129.2, C139.2, R105.1, R111.2
unnamed: C130.2, C140.2, R106.1, R112.2
unnamed: C131.2, C141.2, R107.1, R113.2
unnamed: C132.2, C142.2, R108.1, R114.2
unnamed: C133.2, C143.2, R109.1, R115.2
unnamed: C134.2, C144.2, R110.1, R116.2
unnamed: C136.1, RV18.2
unnamed: C136.2, C137.1, R120.2
unnamed: C147.1, R131.2, RV16.2
unnamed: C147.2, R211.2
unnamed: C149.2, C161.2, R123.1, R132.2
unnamed: C150.2, C162.2, R124.1, R133.2
unnamed: C151.2, C163.2, R125.1, R134.2
unnamed: C152.2, C164.2, R126.1, R135.2
unnamed: C153.2, C165.2, R127.1, R136.2
unnamed: C154.2, C166.2, R128.1, R137.2
unnamed: C167.2, R151.1
unnamed: C169.2, R153.1
unnamed: C171.2, R155.1
unnamed: C173.2, R157.1
unnamed: C175.1, C191.2, R159.1, U18.1
unnamed: C175.2, C176.1, R139.2, R145.2
unnamed: C177.1, C192.2, R160.1, U18.7
unnamed: C177.2, C178.1, R140.2, R146.2
unnamed: C179.1, C193.2, R161.1, U19.1
unnamed: C179.2, C180.1, R141.2, R147.2
unnamed: C181.1, C194.2, R162.1, U19.7
unnamed: C181.2, C182.1, R142.2, R148.2
unnamed: C183.1, C184.2, C185.1, C186.1, R143.2, R149.2
unnamed: C183.2, C184.1, C195.2, R163.1, U20.1
unnamed: C187.1, C188.2, C189.1, C190.1, R144.2, R150.2
unnamed: C187.2, C188.1, C196.2, R164.1, U20.7
unnamed: C191.1, R169.2
unnamed: C192.1, R170.2
unnamed: C193.1, R171.2
unnamed: C194.1, R172.2
unnamed: C195.1, R173.2
unnamed: C196.1, R174.2
unnamed: C197.1, C213.2, R197.1, U21.1
unnamed: C197.2, C198.1, R180.2, R186.2
unnamed: C199.1, C200.2, C201.1, C202.1, R181.2, R187.2
unnamed: C199.2, C200.1, C214.2, R198.1, U21.7
unnamed: C203.1, C215.2, R199.1, U22.1
unnamed: C203.2, C204.1, R182.2, R188.2
unnamed: C205.1, C206.2, C207.1, C208.1, R183.2, R189.2
unnamed: C205.2, C206.1, C216.2, R200.1, U22.7
unnamed: C209.1, C217.2, R201.1, U23.7
unnamed: C209.2, C210.1, R184.2, R190.2
unnamed: C211.1, C218.2, R202.1, U23.1
unnamed: C211.2, C212.1, R185.2, R191.2
unnamed: C213.1, R203.2
unnamed: C214.1, R204.2
unnamed: C215.1, R205.2
unnamed: C216.1, R206.2
unnamed: C217.1, R207.2
unnamed: C218.1, R208.2
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
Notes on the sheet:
aux vol
music FX send
LINE MUSIC INPUT
38Hz to 140Hz
40Hz
place the caps as close as possible to the opamp they're assignated to
50Hz
bass kill
AUX/MIC CROSSOVER 91Hz/239Hz/4168Hz
MUSIC CROSSOVER 91Hz/239Hz/4168Hz
2kHz
GRAPHIC EQ PART2
31Hz
4kHz
high kill
POWER SUPPLY
peak
high vol
5kHz
kick kill
GAIN
bass para freq
MID
connect to chassis
line mute
shelf freq
mid cut/boost
mic vol
TREBLE
125Hz
J11,J12,J13,J14 are connection points for vu meters
aux FX send
bass vol
16kHz
bass cut/boost
3PDT switch for "sub only"
kick vol
GRAPHIC EQ PART1
PHONO PREAMP
500Hz
